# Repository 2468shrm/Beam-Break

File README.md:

# Beam Break

This is a simple IR beam break board intended for direct interfacing
to a roboRIO DIO.

It has a status LED for visual debug and tuning/placement.

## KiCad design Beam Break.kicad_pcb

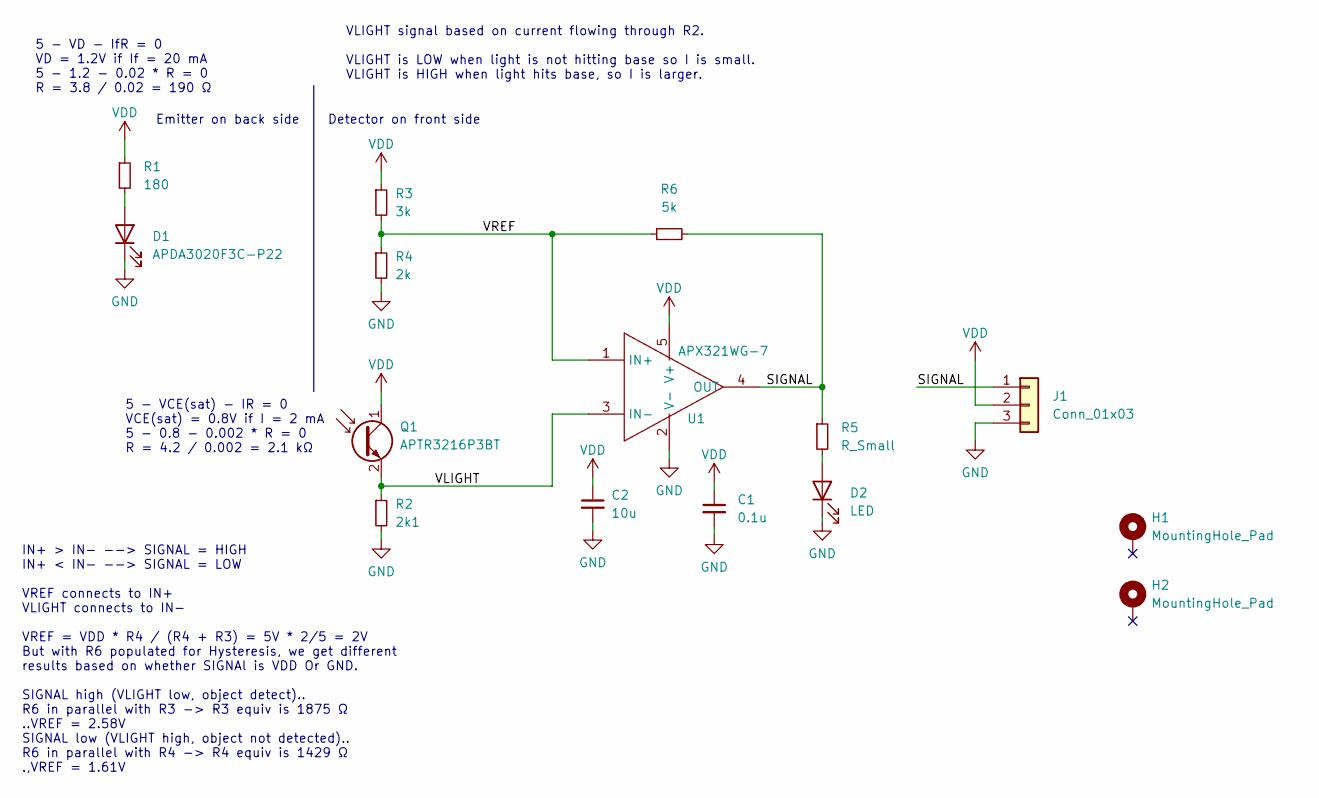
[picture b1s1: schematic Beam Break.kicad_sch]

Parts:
C1: 0.1u; C_1206_3216Metric
C2: 10u; C_1206_3216Metric
D1: APDA3020F3C-P22; APDA3020F3CP22
D2: LED; LED_1206_3216Metric
H1, H2: MountingHole_Pad; MountingHole_2.2mm_M2_DIN965_Pad
J1: Conn_01x03; PinSocket_1x03_P2.54mm_Vertical
Q1: APTR3216P3BT
R1: 180; R_1206_3216Metric
R2: 2k1; R_1206_3216Metric
R3: 3k; R_1206_3216Metric
R4: 2k; R_1206_3216Metric
R5: R_Small; R_1206_3216Metric
R6: 5k; R_1206_3216Metric
U1: APX321WG-7; SOT95P285X145-5N; Manufacturer_Part_Number APX321WG-7; Mouser Part Number 621-APX321WG-7

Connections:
/SIGNAL: J1.1, R5.1, R6.2, U1.4 (OUT)
/VLIGHT: Q1.2 (E), R2.1, U1.3 (IN-)
/VREF: R3.2, R4.1, R6.1, U1.1 (IN+)
GND: C1.2, C2.2, D1.1 (K), D2.1 (K), J1.3, R2.2, R4.2, U1.2 (V-)
unnamed: D1.2 (A), R1.2
unnamed: D2.2 (A), R5.2
VDD: C1.1, C2.1, J1.2, Q1.1 (C), R1.1, R3.1, U1.5 (V+)

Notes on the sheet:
5 - VCE(sat) - IR = 0 VCE(sat) = 0.8V if I = 2 mA 5 - 0.8 - 0.002 * R = 0 R = 4.2 / 0.002 = 2.1 kΩ
Detector on front side
Emitter on back side
IN+ > IN- --> SIGNAL = HIGH IN+ < IN- --> SIGNAL = LOW VREF connects to IN+ VLIGHT connects to IN- VREF = VDD * R4 / (R4 + R3) = 5V * 2/5 = 2V But with R6 populated for Hysteresis, we get different results based on whether SIGNAl is VDD Or GND. SIGNAL high (VLIGHT low, object detect).. R6 in parall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
VLIGHT signal based on current flowing through R2. VLIGHT is LOW when light is not hitting base so I is small. VLIGHT is HIGH when light hits base, so I is larger.
5 - VD - IfR = 0 VD = 1.2V if If = 20 mA 5 - 1.2 - 0.02 * R = 0 R = 3.8 / 0.02 = 190 Ω

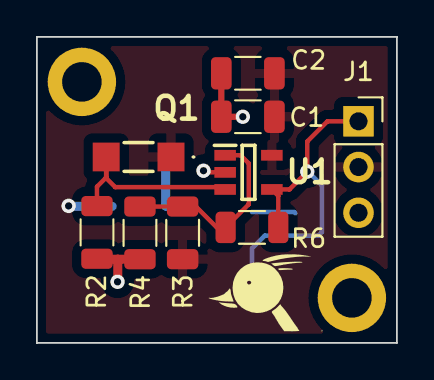
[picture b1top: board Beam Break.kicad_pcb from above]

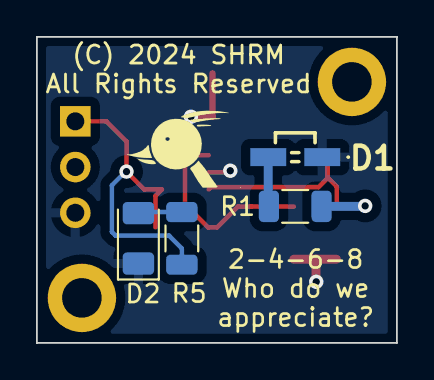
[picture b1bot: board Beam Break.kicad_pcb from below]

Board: 2 copper layers, 20.0 x 17.0 mm, 15 parts (4 on the bottom side), 7 nets.

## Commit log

2024-01-02 initial CAD file commit
2024-01-02 added basic readme
2024-01-02 updated docs

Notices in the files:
Beam Break.kicad_pcb:
(C) 2024 SHRM
All Rights Reserved
